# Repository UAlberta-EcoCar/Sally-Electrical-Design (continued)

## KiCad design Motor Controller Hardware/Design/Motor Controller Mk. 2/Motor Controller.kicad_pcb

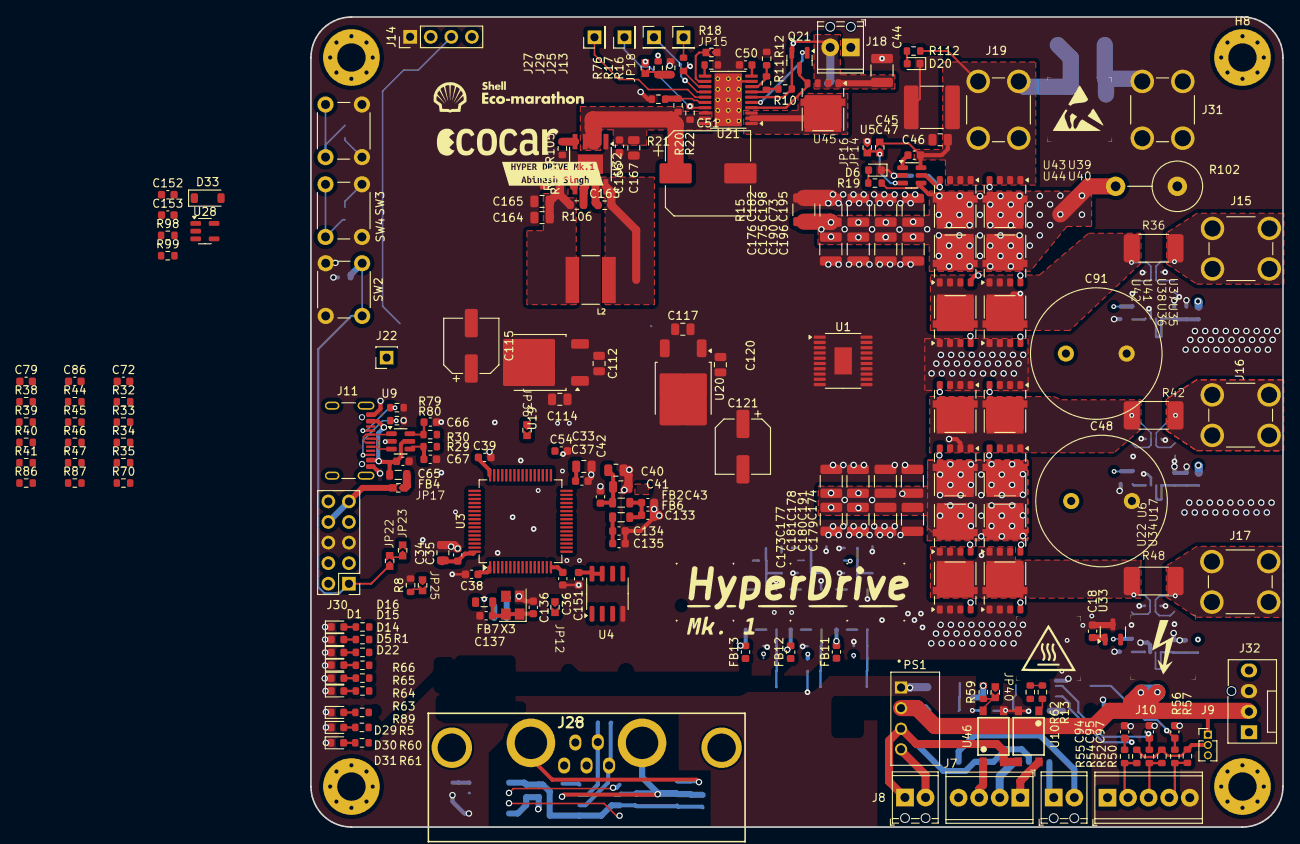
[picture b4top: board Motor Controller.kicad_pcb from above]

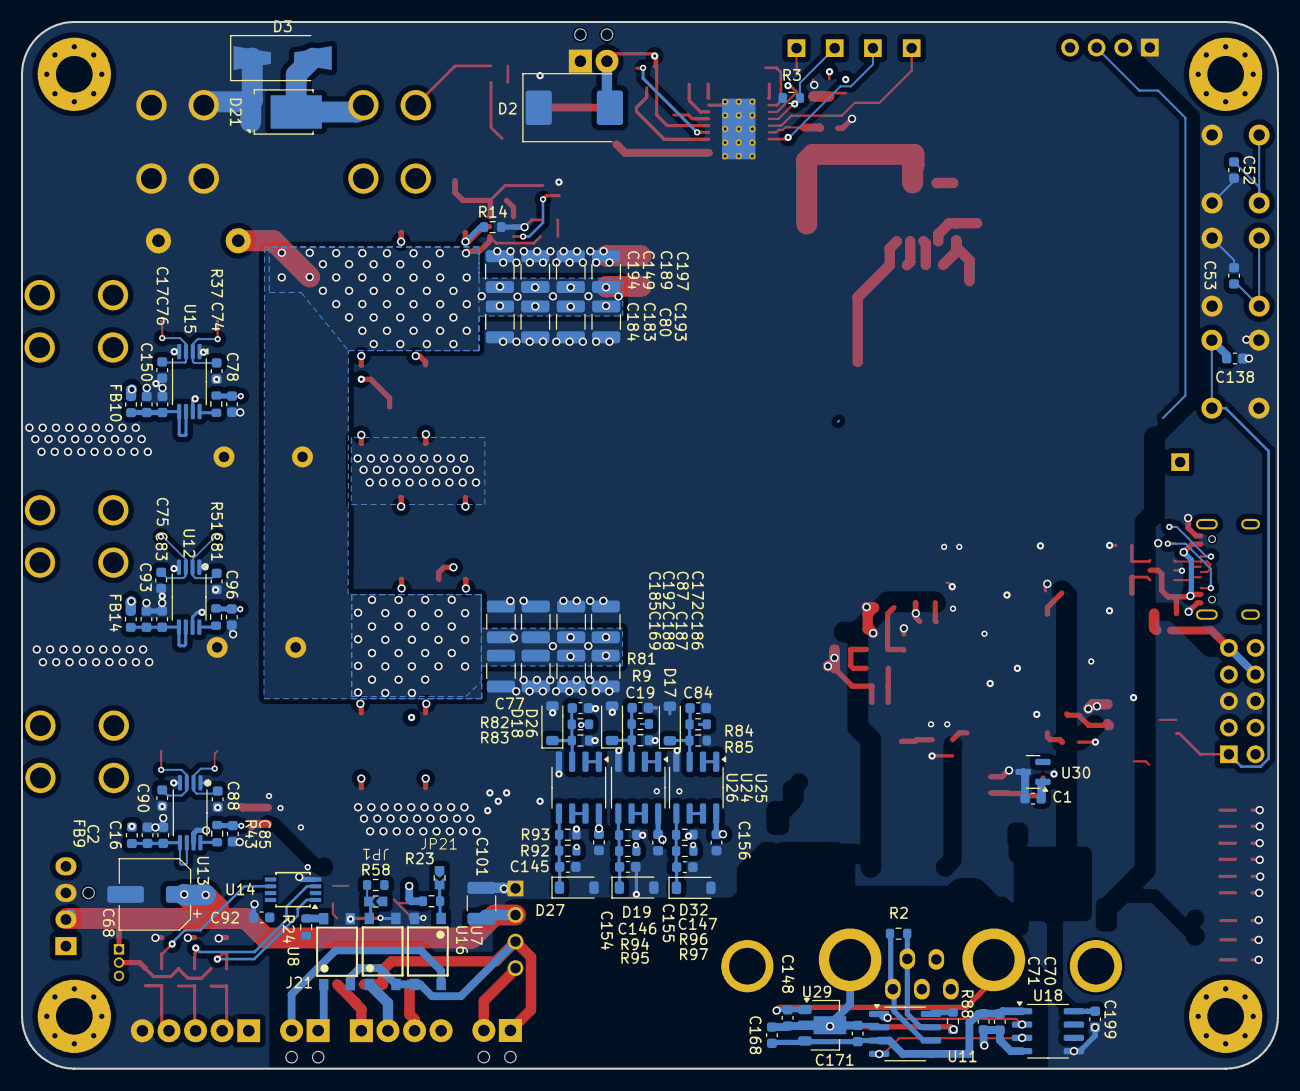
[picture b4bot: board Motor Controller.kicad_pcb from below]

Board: 4 copper layers, 120.0 x 100.0 mm, 320 parts (103 on the bottom side), 167 nets.

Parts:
C1, C2, C16, C17, C18, C35, C36, C37, C38, C39, C42, C43, C47, C50, C52, C53, C54, C65, C70, C71, C75, C92, C93, C133, C135, C136, C137, C138, C150, C151, C153, C154, C155, C156, C166, C171, C199: 100n; C_0603_1608Metric
C19, C77, C84, C145, C146, C147, C152: C; C_0603_1608Metric
C33, C41: 1u; C_0805_2012Metric
C34, C40: 4u7; C_0805_2012Metric
C44, C101, C149, C169, C172, C173, C174, C175, C176, C177, C178, C179, C180, C181, C182, C183, C184, C185, C186, C187, C188, C189, C190, C191, C192, C193, C194, C195, C196, C197, C198: 10u; C_1210_3225Metric
C45: 10u; C_2220_5750Metric
C46: 22n; C_0805_2012Metric
C48, C91: 470u; C_Radial_D16.0mm_H25.0mm_P7.50mm
C51: 100u; CP_Elec_10x10
C66, C67: 47p; C_0603_1608Metric
C68, C115, C121: 100u; CP_Elec_6.3x9.9
C72, C79, C86: 470n; C_0603_1608Metric
C73, C80, C87: 2u2; C_1210_3225Metric
C74, C76, C81, C83, C88, C90: 1n; C_0603_1608Metric
C78, C85, C96: 2n2; C_0603_1608Metric
C94, C95, C97: 100p; C_0603_1608Metric
C112, C114, C117, C120, C165, C167: 10u; C_0805_2012Metric
C134, C148: 1u; C_0603_1608Metric
C163: 100n; R_0603_1608Metric
C164: 47u; C_0805_2012Metric
C168: 2u2; C_0603_1608Metric
D1: GREEN; LED_0603_1608Metric
D2: SMCJ36CA; D_SMC
D3: SMBJ58A; D_SMA-SMB_Universal_Handsoldering
D5, D6, D14, D15, D16, D20, D22, D29, D30, D31: BLUE; LED_0603_1608Metric
D17, D18, D19, D26, D27, D32, D33: MMSZ5226B-7-F; D_SOD-123
D21: D_Schottky; TO-277B
FB2, FB4, FB6, FB7: 600@100MHz 1A; L_0805_2012Metric
FB9, FB10, FB11, FB12, FB13, FB14: 600R@100MHz 1A; L_0603_1608Metric
H7, H8, H9, H10: MountingHole; MountingHole_3.5mm_Pad_Via
J7: Isolated Interface; TerminalBlock_Phoenix_MPT-0,5-4-2.54_1x04_P2.54mm_Horizontal
J8: Interact Power; TerminalBlock_Phoenix_MPT-0,5-2-2.54_1x02_P2.54mm_Horizontal
J9: HALL VCC SEL; PinHeader_1x03_P1.27mm_Vertical
J10: Screw_Terminal_01x03; TerminalBlock_Phoenix_MPT-0,5-5-2.54_1x05_P2.54mm_Horizontal
J11: USB_C_Receptacle_USB2.0_14P; USB_C_Receptacle_GCT_USB4105-xx-A_16P_TopMnt_Horizontal
J13, J25, J27, J29: Conn_01x01_Socket; PinHeader_1x01_P2.54mm_Vertical
J14: Aux Display OLED; PinHeader_1x04_P2.54mm_Vertical
J15: Coil_{U}; KEYSTONE_7691
J16: COIL_{V}; KEYSTONE_7691
J17: COIL_{W}; KEYSTONE_7691
J18: Logic Supply Input; TerminalBlock_Phoenix_MPT-0,5-2-2.54_1x02_P2.54mm_Horizontal
J19: SUPPLY; KEYSTONE_7691
J21: Screw_Terminal_01x02; TerminalBlock_Phoenix_MPT-0,5-2-2.54_1x02_P2.54mm_Horizontal
J22: BUZZER_OUT; PinSocket_1x01_P2.54mm_Vertical
J28: DB7W2-Male
J30: STM32-Prog-Header; PinHeader_2x05_P2.54mm_Vertical
J31: GND; KEYSTONE_7691
J32: Fan; FanPinHeader_1x04_P2.54mm_Vertical
JP1: Controller A EXT Reset EN; J_0603_Triangular
JP12: POWER_STAGE_ENABLE; J_0603_Triangular
JP14: Always ON; J_0603_Triangular
JP15: Active Retry; J_0603_Triangular
JP16: Always OFF; J_0603_Triangular
JP17: Jump 5V; J_0603_Triangular
JP18: ~{SHDN} Enable; J_0603_Triangular
JP21: STATUS_OUT; J_0603_Triangular
JP22: TIE NRST TO EXTNRST; J_0603_Triangular
JP23: SOFTWARE_RESET_CONTROLLER_A; J_0603_Triangular
JP25: BOOT; J_0603_Triangular
JP36, JP40: EXT_DRV_ENABLE; J_0603_Triangular
L2: 22u; IND_ASPI-6045S-2R7N-T
PS1: RFM-0505S; CONV_RFM-0505S
Q21: BSS138; SOT-23
R1: 100R; R_0603_1608Metric
R2: 120R; R_0603_1608Metric
R3: 71k5; R_0603_1608Metric
R5, R19, R37, R43, R50, R51, R54, R56, R60, R61, R63, R64, R65, R66, R89: 1k; R_0603_1608Metric
R8, R14, R34, R35, R40, R41, R46, R47, R76, R81, R83, R85, R88, R99, R104: 10k; R_0603_1608Metric
R9, R82, R84, R98: 147k; R_0603_1608Metric
R10, R11, R12, R16, R17, R18, R20, R21: R; R_0603_1608Metric
R13, R44, R45, R70, R86, R87: 0R; R_0603_1608Metric
R15: 14k; R_1210_3225Metric
R22: 24k; R_0603_1608Metric
R23, R24, R58, R59, R62: 10K; R_0603_1608Metric
R29, R30: 27R; R_0603_1608Metric
R32, R33, R38, R39: 2R2; R_0603_1608Metric
R36, R42, R48: 3m; CSS2H-2512
R52, R55, R57: 4k7; R_0603_1608Metric
R79, R80: 5k1; R_0603_1608Metric
R90: 60k4; R_0603_1608Metric
R92, R94, R96: 5k; R_0603_1608Metric
R93, R95, R97: 9k76; R_0603_1608Metric
R102: 14k; R_Axial_DIN0617_L17.0mm_D6.0mm_P7.62mm_Vertical
R105: 64k9; R_0603_1608Metric
R106: 100k; R_0603_1608Metric
R112: 13k; R_0603_1608Metric
SW2: NRST; SW_PUSH_6mm
SW3: GPBTN_1; SW_PUSH_6mm
SW4: GPBTN_2; SW_PUSH_6mm
U1: DRV8300NPWR; TSSOP-20-1EP_4.4x6.5mm_P0.65mm_EP2.15x3.35mm
U3: STM32G474RET6; LQFP-64_10x10mm_P0.5mm
U4: M95256-WMN6P; SOIC-8_3.9x4.9mm_P1.27mm
U5: LM74700QDBVTQ1; SOT-23-6
U6, U17, U22, U34, U35, U36, U37, U38, U39, U40, U41, U42, U43, U44, U45: NTMFS4D0N08XT1G; PowerMosDFNHybrid
U7, U8, U10, U16, U46: WL-OCPT-140357145200; WL-OCPT_SOP4
U9: USBLC6-2SC6; SOT-23-6
U11: MCP2542FD-E/SN; SOIC-8_3.9x4.9mm_P1.27mm
U12, U13, U15: INA240A3PW; TSSOP-8_4.4x3mm_P0.65mm
U14: 74LVC3G17; TSSOP-8_3x3mm_P0.65mm
U18: ISO6521D; SOIC-8_3.9x4.9mm_P1.27mm
U19: AZ1084-5.0; TO-252-2
U20: AZ1084-3.3; TO-252-2
U21: TPS26631PWP; HTSSOP-20-1EP_4.4x6.5mm_P0.65mm_EP3.4x6.5mm_Mask2.96x2.96mm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
U24, U25, U26: TSV912IDT; SOIC-8_3.9x4.9mm_P1.27mm
U28: TSV911RILT; SOT-23-5
U29: AP2205-5.0; SOT-89-3
U30, U33: MCP9700AT-ETT; SOT-23
U32: LMR38020; TI_SO-PowerPAD-8
X3: 8MHz; Crystal_SMD_3225-4Pin_3.2x2.5mm
kibuzzard-6768F62A: G***; kibuzzard-6768F62A

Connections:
5V_ISOLATED: J8.2, PS1.4 (+VOUT)
+3.3VA: C40.1, C41.1, C42.1, FB2.2, U3.29 (VDDA)
+3V3: C1.2, C18.2, C33.1, C34.1, C35.1, C36.1, C37.1, C38.1, C39.1, C43.1, C92.1, C120.1, C121.1, C133.1, C151.1, C199.1, FB2.1, FB6.1, FB7.2, FB11.1, FB12.1, FB13.1, J9.3, J30.7 (3.3V), J30.10 (5V), R23.2, R24.2, R58.2, R59.2, R61.1, R62.2, U3.1 (VBAT), U3.16 (VDD), U3.32 (VDD), U3.48 (VDD), U3.64 (VDD), U4.7 (~HOLD), U4.8 (VCC), U14.8 (VCC), U18.8 (VCC2), U20.2 (VO), U30.1 (V_{DD}), U33.1 (V_{DD})
+5V: C68.1, C101.1, C114.1, C115.1, C117.1, C153.1, FB9.1, FB10.1, FB14.1, J9.1, J14.2, J30.8 (3.3V), J30.9 (5V), J32.2, JP17.2 (B), PS1.2 (+VIN), R60.1, U19.2 (VO), U20.3 (VI), U28.2 (V+)
+12V: C112.1, C164.1, C165.1, L2.2, R5.1, R90.1, R106.2, U19.3 (VI)
/Comunications/5V: C70.1, C71.1, C168.1, C171.1, U11.3 (VDD), U11.5 (VIO), U18.1 (VCC1), U29.3 (VOUT)
/Comunications/CAN Bus Interface/CAN_H+: J28.2, R2.1, U11.7 (CANH)
/Comunications/CAN Bus Interface/CAN_L-: J28.5, R2.2, U11.6 (CANL)
/Comunications/CAN Bus Interface/CAN_STBY: R88.1, U11.8 (STBY)
/Comunications/CAN Bus Interface/SYS_7V: C148.1, J28.8 (A1), U29.1 (VIN)
/Comunications/CAN Bus Interface/SYS_12V: J28.1, J28.3, J28.4
/Comunications/CAN_RXD_ISO: U3.56 (PB3), U18.6 (OUTB)
/Comunications/CAN_RXD_SYS: U11.4 (RXD), U18.3 (INB)
/Comunications/CAN_TXD_ISO: U3.57 (PB4), U18.7 (INA)
/Comunications/CAN_TXD_SYS: U11.1 (TXD), U18.2 (OUTA)
/Comunications/USB_D+: R29.2, U3.46 (PA12)
/Comunications/USB_D-: R30.2, U3.45 (PA11)
/Controller_B_ANALOG_SPEED: C54.1, R24.1, U3.34 (PB12), U8.4
/Controller_B_STATUS: JP21.1 (A), R1.2, U3.30 (PB10)
/EXT_DRV_EN_IN: JP36.1 (A), JP40.1 (A)
/EXT_NRST_Controllers: JP1.1 (A), JP22.2 (B), JP23.1 (A)
/EXT_POWER_STAGE_EN_IN: JP12.2 (B), JP14.1 (A), JP16.2 (B), U5.3 (EN)
/GATE_DRIVER_FAULT_OUT: R13.1, R62.1, U3.51 (PA15)
/HALL_U: U3.12 (PA0), U14.2 (3Y)
/HALL_V: U3.13 (PA1), U14.5 (2Y)
/HALL_W: U3.14 (PA2), U14.7 (1Y)
/I_{U,_BUFFERED}: U3.20 (PA6), U25.6 (-), U25.7
/I_{V,_BUFFERED}: U3.21 (PA7), U24.6 (-), U24.7
/I_{W,_BUFFERED}: U3.22 (PC4), U26.6 (-), U26.7
/Isolated Driver Interface/Controller_STATUS_ISO: J21.2, U7.4
/Isolated Driver Interface/EXT_ANALOG_SPEED_ISO: J21.1, U8.1
/Isolated Driver Interface/EXT_DRV_EN_IN_ISO: J7.3, U46.1
/Isolated Driver Interface/EXT_NRST_Controllers_IN_ISO: J7.2, U16.1
/Isolated Driver Interface/FAULT_OUT_ISO: J7.1, U10.4
/Low Power Current Monitor: J25.1, R3.1, U3.33 (PB11), U21.14 (IMON)
/Microcontroller/BOOT0: JP25.1 (A), U3.61 (PB8)
/Microcontroller/BUZZER: J22.1, U3.25 (PB1)
/Microcontroller/CLK: U3.5 (PF0), X3.3 (OUT)
/Microcontroller/CNTRL_TMP_SNS: U3.24 (PB0), U30.2 (V_{OUT})
/Microcontroller/GPBTN_1: C52.1, SW3.1, U3.8 (PC0)
/Microcontroller/GPBTN_2: C53.1, JP23.2 (B), SW4.1, U3.55 (PD2)
/Microcontroller/GPLED_1: R89.1, U3.4 (PC15)
/Microcontroller/GPLED_2: R63.1, U3.3 (PC14)
/Microcontroller/GPLED_3: R64.1, U3.2 (PC13)
/Microcontroller/GPLED_4: R65.1, U3.62 (PB9)
/Microcontroller/GPLED_5: R66.1, U3.6 (PF1)
/Microcontroller/I2C3_SCL: J14.3, U3.40 (PC8)
/Microcontroller/I2C3_SDA: J14.4, U3.41 (PC9)
/Microcontroller/NRST: C138.1, J30.1 (RST), JP22.1 (A), SW2.1, U3.7 (PG10)
/Microcontroller/PWR_TMP_SNS: U3.23 (PC5), U33.2 (V_{OUT})
/Microcontroller/SWCLK: J30.2 (SWCLK), U3.50 (PA14)
/Microcontroller/SWDIO: J30.4 (SWDIO), U3.49 (PA13)
/Microcontroller/~MEM_CS: U3.58 (PB5), U4.1 (~S)
/Motor Gate Driver/BSTA: C72.2, U1.20 (BSTA)
/Motor Gate Driver/BSTB: C79.2, U1.17 (BSTB)
/Motor Gate Driver/BSTC: C86.2, U1.14 (BSTC)
/Motor Gate Driver/Coil Drive U/+3V3_Filtered: C154.1, FB11.2, U25.8 (V+)
/Motor Gate Driver/Coil Drive U/COIL_{U}: C76.1, J15.1, R36.2, R82.1, U15.3 (-)
/Motor Gate Driver/Coil Drive U/I_{U}: C78.1, R37.2, R92.1
/Motor Gate Driver/Coil Drive U/V_{SENSE, U, 1}: C74.1, R36.1, R70.2, U15.2 (+), U39.1 (S), U39.2 (S), U39.3 (S), U40.1 (S), U40.2 (S), U40.3 (S), U41.5 (D), U42.5 (D)
/Motor Gate Driver/Coil Drive V/+3V3_Filtered: C155.1, FB12.2, U24.8 (V+)
/Motor Gate Driver/Coil Drive V/COIL_{V}: C83.1, J16.1, R9.1, R42.2, U12.3 (-)
/Motor Gate Driver/Coil Drive V/I_{V}: C96.1, R51.2, R94.1
/Motor Gate Driver/Coil Drive V/V_{SENSE, V, 1}: C81.1, R42.1, R86.2, U12.2 (+), U35.1 (S), U35.2 (S), U35.3 (S), U36.1 (S), U36.2 (S), U36.3 (S), U37.5 (D), U38.5 (D)
/Motor Gate Driver/Coil Drive W/+3V3_Filtered: C156.1, FB13.2, U26.8 (V+)
/Motor Gate Driver/Coil Drive W/COIL_{W}: C90.1, J17.1, R48.2, R84.1, U13.3 (-)
/Motor Gate Driver/Coil Drive W/I_{W}: C85.1, R43.2, R96.1
/Motor Gate Driver/Coil Drive W/VD+: C88.1, R48.1, R87.2, U6.1 (S), U6.2 (S), U6.3 (S), U13.2 (+), U17.1 (S), U17.2 (S), U17.3 (S), U22.5 (D), U34.5 (D)
/Motor Gate Driver/GHA: R32.1, R34.2, U1.19 (GHA)
/Motor Gate Driver/GHB: R38.1, R40.2, U1.16 (GHB)
/Motor Gate Driver/GHC: R44.1, R46.2, U1.13 (GHC)
/Motor Gate Driver/GLA: R33.1, R35.2, U1.11 (GLA)
/Motor Gate Driver/GLB: R39.1, R41.2, U1.10 (GLB)
/Motor Gate Driver/GLC: R45.1, R47.2, U1.9 (GLC)
/Motor Gate Driver/SHA: C72.1, R70.1, U1.18 (SHA)
/Motor Gate Driver/SHB: C79.1, R86.1, U1.15 (SHB)
/Motor Gate Driver/SHC: C86.1, R87.1, U1.12 (SHC)
/Position Sensing/HALL_U_RAW: J10.4, R56.2, R57.1
/Position Sensing/HALL_V_RAW: J10.3, R54.2, R55.1
/Position Sensing/HALL_W_RAW: J10.2, R50.2, R52.1
/Power Delivery/IN_SYS: C44.1, D2.2 (A2), J18.2, Q21.2 (S), R10.1, R16.1, U21.6 (IN_SYS), U45.1 (S), U45.2 (S), U45.3 (S)
/Power Delivery/Motor Supply Unprotected: C45.1, C46.1, C47.2, D3.2 (A2), D21.3 (K), J19.1, JP14.2 (B), R112.1, U5.6 (ANODE), U43.1 (S), U43.2 (S), U43.3 (S), U44.1 (S), U44.2 (S), U44.3 (S)
/Power Delivery/Motor_Controller_Power_Good: J29.1, R22.2, U21.17 (PGOOD)
/Power Delivery/~Low Side Fault: J27.1, U21.15 (~FLT)
/Power Delivery/~SHDN: JP18.1 (A), R76.1, U21.13 (~SHDN)
/SPI_MISO: U3.53 (PC11), U4.2 (Q)
/SPI_MOSI: U3.54 (PC12), U4.5 (D)
/SPI_SCK: U3.52 (PC10), U4.6 (C)
/V_{M}_BUFFERED: U28.1, U28.4 (-)
/V_{SENSE,_U,_BUFFERED}: U3.17 (PA3), U25.1, U25.2 (-)
/V_{SENSE,_V,_BUFFERED}: U3.18 (PA4), U24.1, U24.2 (-)
/V_{SENSE,_W,_BUFFERED}: U3.19 (PA5), U26.1, U26.2 (-)
GND: C1.1, C2.2, C16.2, C17.2, C18.1, C19.2, C33.2, C34.2, C35.2, C36.2, C37.2, C38.2, C39.2, C40.2, C41.2, C42.2, C43.2, C44.2, C45.2, C46.2, C50.2, C51.2, C52.2, C53.2, C54.2, C65.1, C66.2, C67.2, C68.2, C73.2, C74.2, C75.2, C76.2, C77.2, C78.2, C80.2, C81.2, C83.2, C84.2, C85.2, C87.2, C88.2, C90.2, C92.2, C93.2, C94.2, C95.2, C96.2, C97.2, C101.2, C112.2, C114.2, C115.2, C117.2, C120.2, C121.2, C133.2, C134.2, C135.2, C136.2, C137.2, C138.2, C145.2, C146.2, C147.2, C150.2, C151.2, C152.2, C153.2, C154.2, C155.2, C156.2, C164.2, C165.2, C166.2, C167.2, C199.2, D1.1 (K), D2.1 (A1), D3.1 (A1), D5.1 (K), D6.1 (K), D14.1 (K), D15.1 (K), D16.1 (K), D17.2 (A), D18.2 (A), D19.2 (A), D20.1 (K), D21.1 (A), D21.2 (A), D22.1 (K), D26.2 (A), D27.2 (A), D29.1 (K), D30.1 (K), D31.1 (K), D32.2 (A), D33.2 (A), J10.5, J11.A1 (GND), J11.A12 (GND), J11.B1 (GND), J11.B12 (GND), J14.1, J18.1, J30.5 (GND), J30.6 (GND), J31.1, J32.3, JP15.1 (A), JP16.1 (A), PS1.1 (-VIN), R3.2, R8.2, R12.2, R14.2, R17.2, R18.2, R21.2, R34.1, R35.1, R40.1, R41.1, R46.1, R47.1, R79.2, R80.2, R81.1, R83.1, R85.1, R93.1, R95.1, R97.1, R99.1, R104.2, R105.2, SW2.2, SW3.2, SW4.2, U1.8 (GND), U3.15 (VSS), U3.27 (VSSA), U3.31 (VSS), U3.47 (VSS), U3.63 (VSS), U4.4 (VSS), U5.2 (GND), U7.2, U8.3, U9.2 (GND), U10.2, U12.1 (GND), U12.4 (GND), U12.7 (REF1), U13.1 (GND), U13.4 (GND), U13.7 (REF1), U14.4 (GND), U15.1 (GND), U15.4 (GND), U15.7 (REF1), U16.3, U18.5 (GND2), U19.1 (GND), U20.1 (GND), U21.9 (GND), U21.21 (GND), U22.1 (S), U22.2 (S), U22.3 (S), U24.4 (V-), U25.4 (V-), U26.4 (V-), U28.5 (V-), U30.3 (GND), U32.1 (GND), U32.9 (EP), U33.3 (GND), U34.1 (S), U34.2 (S), U34.3 (S), U37.1 (S), U37.2 (S), U37.3 (S), U38.1 (S), U38.2 (S), U38.3 (S), U41.1 (S), U41.2 (S), U41.3 (S), U42.1 (S), U42.2 (S), U42.3 (S), U46.3, X3.2 (GND)
GND1: J8.1, PS1.3 (-VOUT), U7.3, U8.2, U10.3, U16.2, U46.2
GND2: C70.2, C71.2, C148.2, C168.2, C171.2, J28.9 (A2), R88.2, U11.2 (VSS), U18.4 (GND1), U29.2 (GND)
GNDPWR: C48.2, C91.2, C149.2, C169.2, C172.2, C173.2, C174.2, C175.2, C176.2, C177.2, C178.2, C179.2, C180.2, C181.2, C182.2, C183.2, C184.2, C185.2, C186.2, C187.2, C188.2, C189.2, C190.2, C191.2, C192.2, C193.2, C194.2, C195.2, C196.2, C197.2, C198.2, R15.2, R102.1
Logic Power Protected: C51.1, C166.1, C167.1, R20.1, R22.1, U21.18 (OUT), U21.19 (OUT), U21.20 (OUT), U32.2 (EN), U32.3 (VIN)
unnamed: C66.1, R30.1, U9.6 (I/O1)
unnamed: C67.1, R29.1, U9.4 (I/O2)
unnamed: D1.2 (A), R1.1
unnamed: D5.2 (A), R63.2
unnamed: D6.2 (A), R19.2
unnamed: R44.2, U6.4 (G), U17.4 (G)
unnamed: R38.2, U35.4 (G), U36.4 (G)
unnamed: R39.2, U37.4 (G), U38.4 (G)
unnamed: R32.2, U39.4 (G), U40.4 (G)
unnamed: R33.2, U41.4 (G), U42.4 (G)
unnamed: R45.2, U22.4 (G), U34.4 (G)
unnamed: D14.2 (A), R64.2
unnamed: D15.2 (A), R65.2
unnamed: D16.2 (A), R66.2
unnamed: C84.1, D17.1 (K), R84.2, R85.2, U26.3 (+)
unnamed: C19.1, D18.1 (K), R9.2, R81.2, U24.3 (+)
unnamed: C146.1, D19.1 (K), R94.2, R95.2, U24.5 (+)
unnamed: D20.2 (A), R112.2
unnamed: D22.2 (A), R89.2
unnamed: C77.1, D26.1 (K), R82.2, R83.2, U25.3 (+)
unnamed: C145.1, D27.1 (K), R92.2, R93.2, U25.5 (+)
unnamed: D29.2 (A), R5.2
unnamed: D30.2 (A), R60.2
unnamed: D31.2 (A), R61.2
unnamed: C147.1, D32.1 (K), R96.2, R97.2, U26.5 (+)
unnamed: C152.1, D33.1 (K), R98.2, R99.2, U28.3 (+)
unnamed: J9.2, J10.1, R52.2, R55.2, R57.2
unnamed: J11.A5 (CC1), R79.1
unnamed: J11.B5 (CC2), R80.1
unnamed: J11.A6 (D+), J11.B6 (D+), U9.3 (I/O2)
unnamed: J11.A7 (D-), J11.B7 (D-), U9.1 (I/O1)
unnamed: J13.1, R76.2
unnamed: JP1.2 (B), R58.1, U16.4
unnamed: JP12.1 (A), U3.26 (PB2)
unnamed: JP15.2 (B), U21.12 (MODE)
unnamed: JP18.2 (B), R16.2, R17.1
unnamed: JP21.2 (B), R23.1, U7.1
unnamed: JP25.2 (B), R8.1
unnamed: JP36.2 (B), U3.39 (PC7)
unnamed: JP40.2 (B), R59.1, U46.4
unnamed: Q21.3 (D), U21.4 (B_GATE), U45.4 (G)
unnamed: Q21.1 (G), U21.5 (DRV)
unnamed: R13.2, U10.1
unnamed: R37.1, U15.8
unnamed: R43.1, U13.8
unnamed: R51.1, U12.8
unnamed: C47.1, U5.1 (VCAP)
unnamed: C65.2, FB4.1, J11.A4 (VBUS), J11.A9 (VBUS), J11.B4 (VBUS), J11.B9 (VBUS), U9.5 (VBUS)
unnamed: C75.1, C93.1, FB14.2, U12.5 (V+), U12.6 (REF2)
unnamed: C2.1, C16.1, FB9.2, U13.5 (V+), U13.6 (REF2)
unnamed: C94.1, R50.1, U14.1 (1A)
unnamed: C95.1, R54.1, U14.3 (2A)
unnamed: C97.1, R56.1, U14.6 (3A)
unnamed: C17.1, C150.1, FB10.2, U15.5 (V+), U15.6 (REF2)
unnamed: R18.1, U21.11 (ILIM)
unnamed: R11.2, R12.1, U21.8 (OVP)
unnamed: R20.2, R21.1, U21.16 (PGTH)
unnamed: R10.2, R11.1, U21.7 (UVLO)
unnamed: C50.1, U21.10 (dVdT)
unnamed: C163.1, U32.7 (BOOT)
unnamed: R90.2, R104.1, U32.5 (FB)
unnamed: R106.1, U32.6 (PG)
unnamed: R105.1, U32.4 (RT/SYNC)
unnamed: C163.2, L2.1, U32.8 (SW)
unnamed: R14.1, U5.5 (GATE), U43.4 (G), U44.4 (G)
unnamed: U21.1 (IN), U21.2 (IN), U21.3 (IN), U45.5 (D)
unnamed: C136.1, C137.1, FB7.1, X3.1 (EN), X3.4 (Vdd)
VBUS: FB4.2, JP17.1 (A)
VREFP: C134.1, C135.1, FB6.2, U3.28 (VREF+)
V_{M}: C48.1, C73.1, C80.1, C87.1, C91.1, C149.1, C169.1, C172.1, C173.1, C174.1, C175.1, C176.1, C177.1, C178.1, C179.1, C180.1, C181.1, C182.1, C183.1, C184.1, C185.1, C186.1, C187.1, C188.1, C189.1, C190.1, C191.1, C192.1, C193.1, C194.1, C195.1, C196.1, C197.1, C198.1, R15.1, R19.1, R98.1, R102.2, U5.4 (CATHODE), U6.5 (D), U17.5 (D), U35.5 (D), U36.5 (D), U39.5 (D), U40.5 (D), U43.5 (D), U44.5 (D)

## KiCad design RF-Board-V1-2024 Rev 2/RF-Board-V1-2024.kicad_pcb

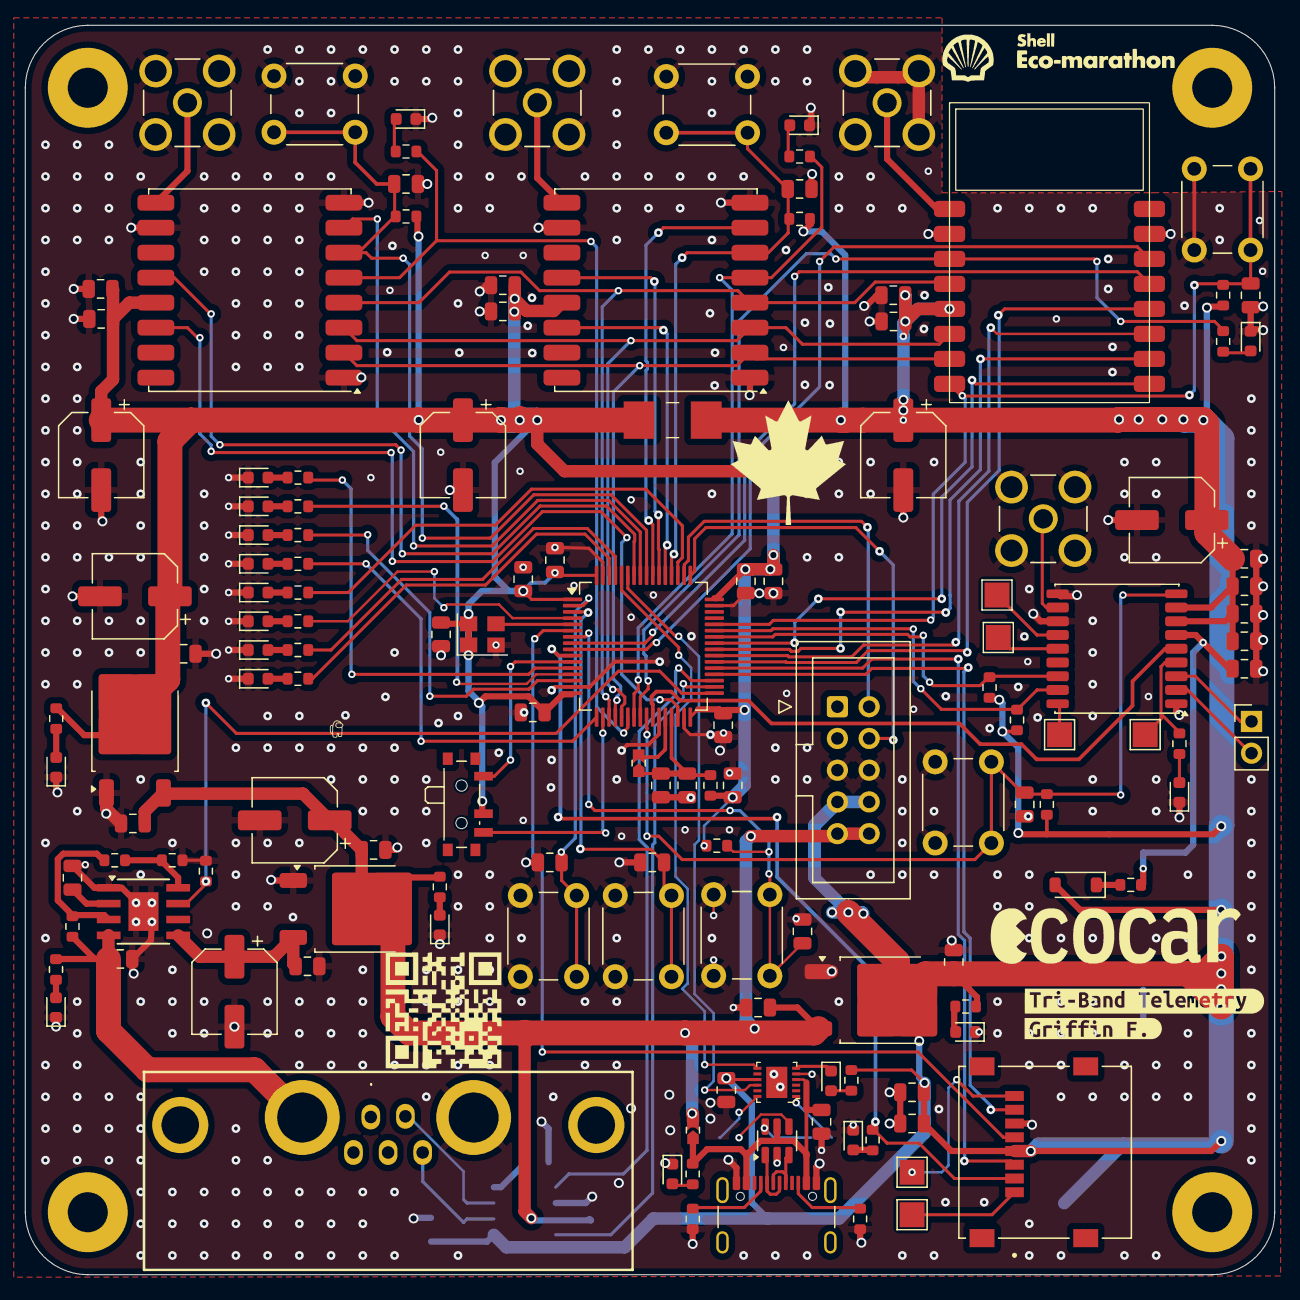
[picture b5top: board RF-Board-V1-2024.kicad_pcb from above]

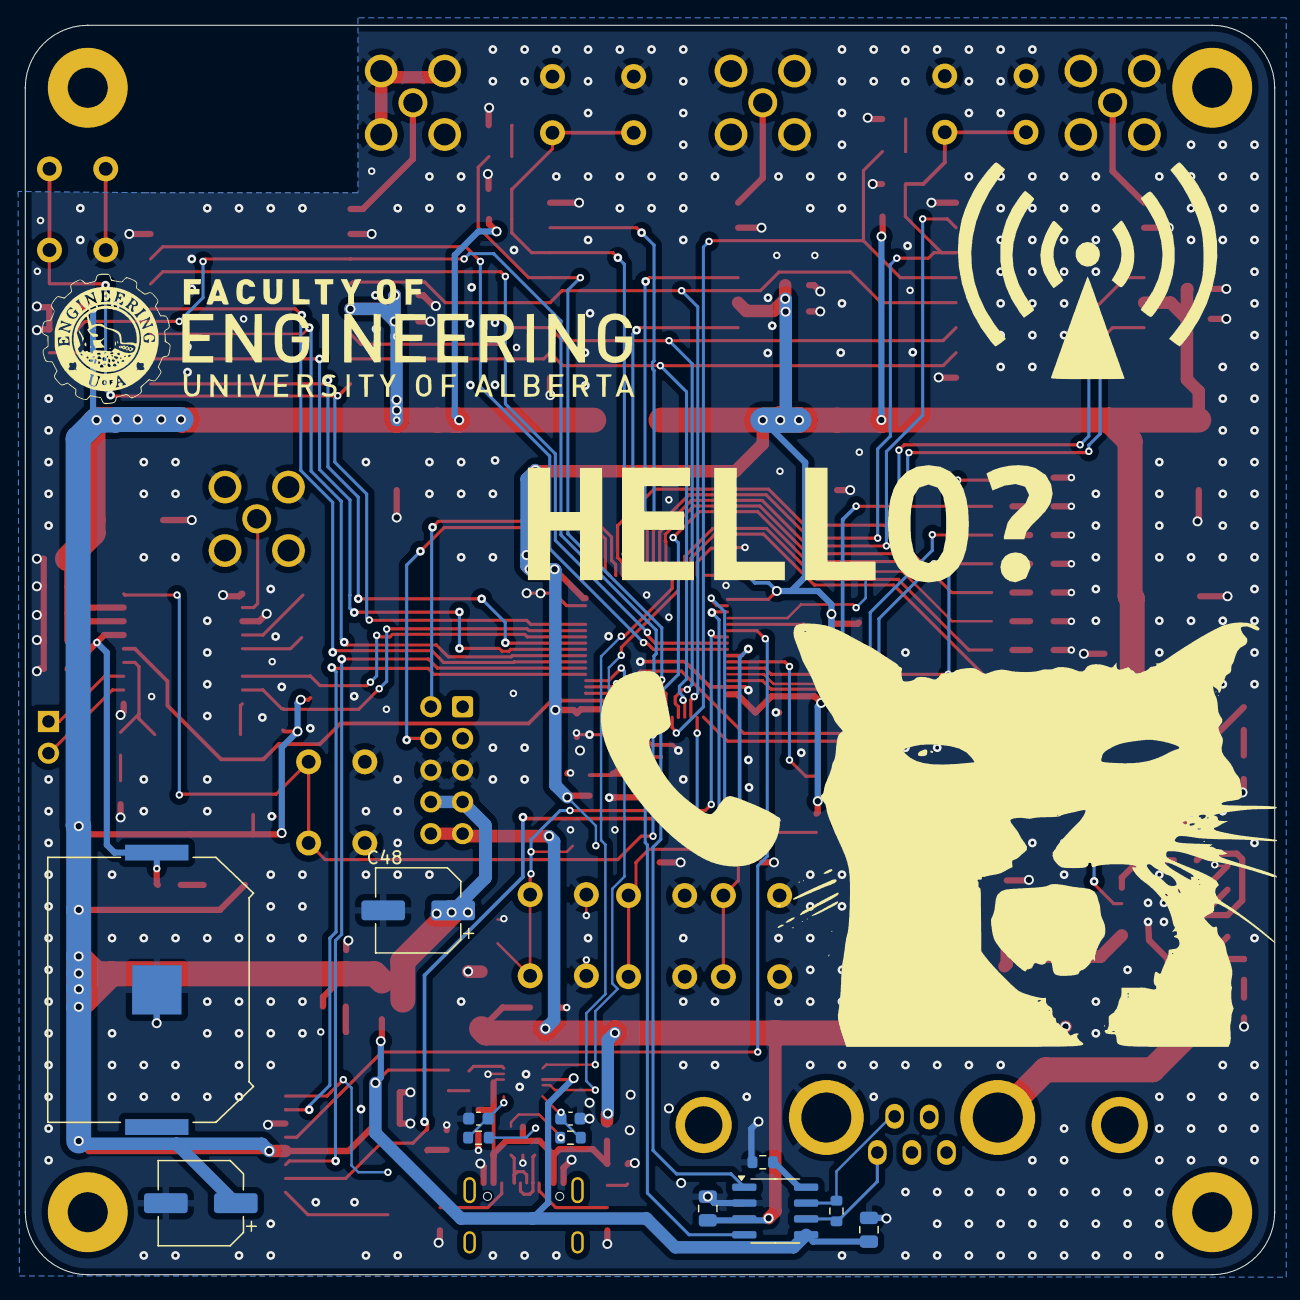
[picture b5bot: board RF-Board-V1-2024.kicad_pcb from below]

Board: 2 copper layers, 100.0 x 100.0 mm, 158 parts (13 on the bottom side), 106 nets.

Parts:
BT1: 3034TR; BAT_3034TR
C1, C9, C12, C15, C16, C18, C22, C39, C46: 10u; C_0805_2012Metric
C2, C10, C47: 22u; C_0805_2012Metric
C3, C4, C8, C14, C17, C31, C32, C40, C48: 100u; CP_Elec_6.3x5.9
C5, C29, C30, C42: 1u; C_0805_2012Metric
C6, C11, C13, C19, C20, C21, C23, C24, C25, C26, C27, C28, C33, C34, C35, C36, C37, C38, C41, C43, C44, C45, C49, C50, C53: 100n; C_0805_2012Metric
C7: 2n2; C_0805_2012Metric
C51, C52: 47p; C_0603_1608Metric
D1, D3, D4, D5, D6, D8, D9, D10, D11, D12, D13, D14, D15, D16, D17, D18, D19, D20: LED; LED_0603_1608Metric
D2: BLUE; LED_0603_1608Metric
D7: 0.5A/40V/420mV; D_SOD-123
FB2: 120R; R_0603_1608Metric
H1, H2, H3, H4: MountingHole_3.2mm_M3_Pad
J1: DB7W2-Male
J2, J3, J6: RFPC-SMA29-F; GRADCONN_RFPC-SMA29-F
J4: UART; PinHeader_1x02_P2.54mm_Vertical
J5: RFPC-SMA28-F; GRADCONN_RFPC-SMA28-F
J7: STM32-Prog-Header; IDC-STM32-Prog-Header_2x05_P2.54mm_Vertical
J8: USB_C_Receptacle_USB2.0_14P; USB_C_Receptacle_GCT_USB4105-xx-A_16P_TopMnt_Horizontal
J9: MSD-10-C; CUI_MSD-10-C
JP1, JP2: Jumper_2_Open; J_0603_Triangular
JP4: Jumper_2_Open; Jumper_Micro-Miniature_P5.375mm
R1, R2: 5k1; R_0603_1608Metric
R3, R21: 2k; R_0603_1608Metric
R4: 150; R_0603_1608Metric
R5: 120; R_0603_1608Metric
R6: 287K; R_0603_1608Metric
R7: 57K; R_0603_1608Metric
R8: 47k; R_0603_1608Metric
R9: 1k1; R_0603_1608Metric
R10, R12, R14, R15, R17, R18, R31, R34: 600; R_0603_1608Metric
R11, R13: 2k2; R_0603_1608Metric
R16: 3k3; R_0603_1608Metric
R19, R26: 10k; R_0603_1608Metric
R20, R22, R23, R24, R25, R30, R32, R33, R37: 1k; R_0603_1608Metric
R27, R28, R29: 0R; R_0603_1608Metric
R35, R36: 27R; R_0603_1608Metric
RF1: MAX-M10S; ublox_MAX
RF2: VG2392S240X0M2; Vollgo VG2392S240X0M2
RF3: DL-RFM69HC-915M; HOPERF_RFM9XW_SMD
RF4: RFM95W-868S2; HOPERF_RFM9XW_SMD
SW1, SW2, SW3, SW4, SW5, SW6, SW8: SW_SPST; SW_PUSH_6mm
SW7: SW_DPDT_x2; SW_SPDT_PCM12
TP1, TP2, TP3, TP4, TP5, TP6: TestPoint; TestPoint_Pad_2.0x2.0mm
U1, U2: AZ1084-3.3; TO-252-2
U3: TPS2596; TI_SO-PowerPAD-8
U4: AZ1084-5.0; TO-252-2
U5: MCP2542FD; SOIC-8_3.9x4.9mm_P1.27mm
U6: STM32G484RET6; LQFP-64_10x10mm_P0.5mm
U7: USBLC6-2SC6; SOT-23-6
U8: FT234XD-R; DFN-12-1EP_3x3mm
X1: OXETDLJANF-8MHZ; Crystal_SMD_3225-4Pin_3.2x2.5mm
kibuzzard-679868A6: G***; kibuzzard-679868A6
kibuzzard-6798610B: G***; kibuzzard-6798610B
kibuzzard-6798611E: G***; kibuzzard-6798611E

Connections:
+3.3V: C2.1, C4.1, C11.2, C12.2, C13.1, C14.1, C15.2, C16.2, C17.1, C18.2, C19.2, C20.2, C21.2, C22.1, C23.1, C24.1, C25.1, C26.1, C27.1, C30.1, C31.1, C32.1, C33.2, C34.2, C35.2, C39.2, C40.1, C41.2, C47.1, C48.1, C49.1, D7.2 (A), FB2.2, J7.7 (3.3V), J7.8 (3.3V), J9.04 (VDD), JP4.1 (A), JP4.2 (B), R10.1, R11.1, R13.1, R26.1, R27.1, R28.1, R29.1, R31.1, R34.1, R37.2, RF1.7 (VCC_IO), RF1.8 (VCC), RF2.5 (VCC), RF3.13 (3.3V), RF4.13 (3.3V), SW7.2 (B), U1.2 (VO), U2.2 (VO), U5.5 (VIO), U6.1 (VBAT), U6.16 (VDD), U6.32 (VDD), U6.48 (VDD), U6.64 (VDD), U8.9 (VCCIO), X1.1 (Tri-State), X1.4 (VDD)
+5V: C1.1, C3.1, C5.1, C10.1, C46.1, J7.9 (5V), J7.10 (5V), JP1.2 (B), R3.1, U1.3 (VI), U2.3 (VI), U4.2 (VO), U5.3 (VDD)
/24.BUSY: RF2.9 (BUSY), U6.41 (PC9)
/24.DIO1: RF2.10 (DIO1), U6.40 (PC8)
/24.DIO2: RF2.11 (DIO2), U6.39 (PC7)
/24.DIO3: RF2.12 (DIO3), U6.38 (PC6)
/24.NSS: R18.1, RF2.3 (NSS), U6.24 (PB0)
/24.RST: C44.1, R27.2, RF2.8 (RST), SW5.2 (B), U6.44 (PA10)
/24.RXEN: RF2.14 (RXEN), U6.9 (PC1)
/24.TXEN: RF2.13 (TXEN), U6.8 (PC0)
/868.DIO0: RF4.14 (DIO0), U6.53 (PC11)
/868.DIO4: RF4.12 (DIO4), U6.54 (PC12)
/868.DIO5: RF4.7 (DIO5), U6.55 (PD2)
/868.MISO: RF2.7 (MISO), RF3.2 (MISO), RF4.2 (MISO), U6.20 (PA6)
/868.MOSI: RF2.6 (MOSI), RF3.3 (MOSI), RF4.3 (MOSI), U6.21 (PA7)
/868.NSS: R12.1, RF4.5 (NSS), U6.23 (PC5)
/868.RST: C45.1, R29.2, RF4.6 (RESET), SW6.2 (B), U6.52 (PC10)
/868.SCK: RF2.4 (SCK), RF3.4 (SCK), RF4.4 (SCK), U6.19 (PA5)
/915.DIO0: RF3.14 (DIO0), U6.30 (PB10)
/915.DIO4: RF3.12 (DIO4), U6.58 (PB5)
/915.DIO5: RF3.7 (DIO5), U6.57 (PB4)
/915.NSS: R15.1, RF3.5 (NSS), U6.22 (PC4)
/915.RST: C38.1, R28.2, RF3.6 (RESET), SW3.2 (B), U6.56 (PB3)
/CAN_RX: U5.4 (RXD), U6.34 (PB12)
/CAN_TX: U5.1 (TXD), U6.35 (PB13)
/GNSS.EXTINT: RF1.5 (EXTINT), U6.26 (PB2)
/GNSS.I2CSCL: R13.2, RF1.17 (SCL), U6.43 (PA9)
/GNSS.I2CSDA: R11.2, RF1.16 (SDA), U6.42 (PA8)
/GPIO_BTN1: C36.1, SW1.2 (B), U6.2 (PC13)
/GPIO_BTN2: C37.1, SW2.2 (B), U6.3 (PC14)
/GPIO_LED1: R20.2, U6.12 (PA0)
/GPIO_LED2: R22.2, U6.13 (PA1)
/GPIO_LED3: R23.2, U6.14 (PA2)
/GPIO_LED4: R24.2, U6.17 (PA3)
/GPIO_LED5: R25.2, U6.51 (PA15)
/GPIO_LED6: R30.2, U6.4 (PC15)
/GPIO_LED7: R32.2, U6.61 (PB8)
/GPIO_LED8: R33.2, U6.62 (PB9)
/GPIO_SWT1: SW7.1 (A), U6.11 (PC3)
/GPIO_SWT2: SW7.3 (C), U6.18 (PA4)
/IMON: R9.1, U3.7 (ILM), U6.33 (PB11)
/NRESET: C53.1, R37.1, SW8.2 (B), U6.7 (PG10)
/Power_CAN/7V_UnProtected: C6.1, J1.8 (A1), R4.1, R6.2, U3.4 (IN)
/Power_CAN/CAN_H: J1.2, R5.1, U5.7 (CANH)
/Power_CAN/CAN_L: J1.5, R5.2, U5.6 (CANL)
/Power_CAN/CC1: J8.A5 (CC1), R1.1
/Power_CAN/CC2: J8.B5 (CC2), R2.1
/Power_CAN/FUSE_OUT: C8.1, C9.1, U3.5 (OUT), U4.3 (VI)
/Power_CAN/USBDM: R35.1, U7.6 (I/O1)
/Power_CAN/USBDP: R36.1, U7.4 (I/O2)
/Power_CAN/VBUS: C50.1, J8.A4 (VBUS), J8.A9 (VBUS), J8.B4 (VBUS), J8.B9 (VBUS), JP1.1 (A), R21.1, U7.5 (VBUS), U8.4 (VCC)
/RF-915-868/ANT_868: J3.1, RF4.9 (ANT)
/RF-915-868/ANT_915: J2.1, RF3.9 (ANT)
/RF-GNSS_2.4Lora/BACKUP: BT1.P1, C42.1, R16.2, RF1.6 (V_BCKP)
/RF-GNSS_2.4Lora/TP: R17.1, RF1.4 (TIMEPULSE), TP1.1
/SD.MISO: J9.07 (DAT0), U6.36 (PB14)
/SD.MOSI: J9.03 (CMD), U6.37 (PB15)
/SD.NSS: J9.02 (CD/DAT3), R14.2, U6.10 (PC2)
/SD.SCLK: J9.05 (CLK), U6.6 (PF1)
/SW_CLK: J7.2 (SWCLK), U6.50 (PA14)
/SW_DIO: J7.4 (SWDIO), U6.49 (PA13)
/USART1_RX: U6.60 (PB7), U8.7 (TXD)
/USART1_TX: U6.59 (PB6), U8.10 (RXD)
/VDDA: C28.1, C29.1, FB2.1, JP2.1 (A), U6.29 (VDDA)
/XCLK: U6.5 (PF0), X1.3 (OUT)
/~GNSS.RST: C43.1, R26.2, RF1.9 (~RESET), SW4.2 (B), U6.25 (PB1)
GND: BT1.N, C1.2, C2.2, C3.2, C4.2, C5.2, C6.2, C7.2, C8.2, C9.2, C10.2, C11.1, C12.1, C13.2, C14.2, C15.1, C16.1, C17.2, C18.1, C19.1, C20.1, C21.1, C22.2, C23.2, C24.2, C25.2, C26.2, C27.2, C28.2, C29.2, C30.2, C31.2, C32.2, C33.1, C34.1, C35.1, C36.2, C37.2, C38.2, C39.1, C40.2, C41.1, C42.2, C43.2, C44.2, C45.2, C46.2, C47.2, C48.2, C49.2, C50.2, C51.1, C52.1, C53.2, D1.1 (K), D2.1 (K), D3.1 (K), D4.1 (K), D5.1 (K), D6.1 (K), D8.1 (K), D9.1 (K), D10.1 (K), D11.1 (K), D12.1 (K), D13.1 (K), D14.1 (K), D15.1 (K), D16.1 (K), D17.1 (K), D18.1 (K), D19.1 (K), J1.9 (A2), J2.G1, J2.G2, J2.G3, J2.G4, J3.G1, J3.G2, J3.G3, J3.G4, J5.G1, J5.G2, J5.G3, J5.G4, J6.G1, J6.G2, J6.G3, J6.G4, J7.5 (GND), J7.6 (GND), J8.A1 (GND), J8.A12 (GND), J8.B1 (GND), J8.B12 (GND), J9.06 (VSS), R1.2, R2.2, R8.2, R9.2, R19.2, RF1.1 (GND), RF1.10 (GND), RF1.12 (GND), RF2.2 (GND), RF2.15 (GND), RF3.1 (GND), RF3.8 (GND), RF3.10 (GND), RF4.1 (GND), RF4.8 (GND), RF4.10 (GND), SW1.1 (A), SW2.1 (A), SW3.1 (A), SW4.1 (A), SW5.1 (A), SW6.1 (A), SW8.1 (A), U1.1 (GND), U2.1 (GND), U3.1 (GND), U3.9 (PAD), U4.1 (GND), U5.2 (VSS), U6.15 (VSS), U6.27 (VSSA), U6.31 (VSS), U6.47 (VSS), U6.63 (VSS), U7.2 (GND), U8.5 (GND), U8.13 (GND), X1.2 (GND)
unnamed: D1.2 (A), R3.2
unnamed: D2.2 (A), R4.2
unnamed: D3.2 (A), R10.2
unnamed: D4.2 (A), R12.2
unnamed: D5.2 (A), R14.1
unnamed: D6.2 (A), R15.2
unnamed: D7.1 (K), R16.1
unnamed: D8.2 (A), R17.2
unnamed: D9.2 (A), R18.2
unnamed: D10.2 (A), R21.2
unnamed: D11.2 (A), R20.1
unnamed: D12.2 (A), R22.1
unnamed: D13.2 (A), R23.1
unnamed: D14.2 (A), R24.1
unnamed: D15.2 (A), R25.1
unnamed: D16.2 (A), R30.1
unnamed: D17.2 (A), R31.2
unnamed: D18.2 (A), R32.1
unnamed: D19.2 (A), R33.1
unnamed: D20.2 (A), R34.2
unnamed: D20.1 (K), U8.6 (CBUS0)
unnamed: J4.1, RF1.3 (RXD)
unnamed: J4.2, RF1.2 (TXD)
unnamed: J8.A6 (D+), J8.B6 (D+), U7.3 (I/O2)
unnamed: J8.A7 (D-), J8.B7 (D-), U7.1 (I/O1)
unnamed: J9.08 (DAT1), TP6.1
unnamed: J9.01 (DAT2), TP5.1
unnamed: JP2.2 (B), U6.28 (VREF+)
unnamed: RF1.13 (LNA_EN), TP4.1
unnamed: J5.1, RF1.11 (RF_IN)
unnamed: RF1.14 (VCC_RF), TP3.1
unnamed: RF1.18 (~SAFEBOOT), TP2.1
unnamed: J6.1, RF2.1 (ANT)
unnamed: R6.1, R7.1, U3.3 (EN/UVLO)
unnamed: R7.2, R8.1, U3.8 (OVLO)
unnamed: C7.1, U3.2 (dV/dT)
unnamed: R19.1, U5.8 (STBY)
unnamed: C51.2, R35.2, U8.1 (USBDM)
unnamed: C52.2, R36.2, U8.12 (USBDP)

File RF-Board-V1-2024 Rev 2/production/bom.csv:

Designator,Footprint,Quantity,Value,LCSC Part #
BT1,BAT_3034TR,1,3034TR,
"C1, C12, C15, C16, C18, C22, C39, C46, C9",0805,9,10u,
"C10, C2, C47",0805,3,22u,
"C11, C13, C19, C20, C21, C23, C24, C25, C26, C27, C28, C33, C34, C35, C36, C37, C38, C41, C43, C44, C45, C49, C50, C53, C6",0805,25,100n,
"C14, C17, C3, C31, C32, C4, C40, C48, C8",CP_Elec_6.3x5.9,9,100u,
"C29, C30, C42, C5",0805,4,1u,
"C51, C52",0603,2,47p,
C7,0805,1,2n2,
"D1, D10, D11, D12, D13, D14, D15, D16, D17, D18, D19, D20, D3, D4, D5, D6, D8, D9",0603,18,LED,
D2,0603,1,BLUE,
D7,D_SOD-123,1,0.5A/40V/420mV,
FB2,0603,1,120R,
"H1, H2, H3, H4",MountingHole_3.2mm_M3_Pad,4,~,
J1,DB7W2-Male,1,~,
"J2, J3, J6",GRADCONN_RFPC-SMA29-F,3,RFPC-SMA29-F,
J4,PinHeader_1x02_P2.54mm_Vertical,1,UART,
J5,GRADCONN_RFPC-SMA28-F,1,RFPC-SMA28-F,
J7,IDC-STM32-Prog-Header_2x05_P2.54mm_Vertical,1,STM32-Prog-Header,
J8,USB_C_Receptacle_GCT_USB4105-xx-A_16P_TopMnt_Horizontal,1,USB_C_Receptacle_USB2.0_14P,
J9,CUI_MSD-10-C,1,MSD-10-C,
"JP1, JP2",J_0603_Triangular,2,Jumper_2_Open,
JP4,Jumper_Micro-Miniature_P5.375mm,1,Jumper_2_Open,
"R1, R2",0603,2,5k1,
"R10, R12, R14, R15, R17, R18, R31, R34",0603,8,600,
"R11, R13",0603,2,2k2,
R16,0603,1,3k3,
"R19, R26",0603,2,10k,
"R20, R22, R23, R24, R25, R30, R32, R33, R37",0603,9,1k,
"R21, R3",0603,2,2k,
"R27, R28, R29",0603,3,0R,
"R35, R36",0603,2,27R,
R4,0603,1,150,
R5,0603,1,120,
R6,0603,1,287K,
R7,0603,1,57K,
R8,0603,1,47k,
R9,0603,1,1k1,
RF1,ublox_MAX,1,MAX-M10S,
RF2,Vollgo VG2392S240X0M2,1,VG2392S240X0M2,
RF3,HOPERF_RFM9XW_SMD,1,DL-RFM69HC-915M,
RF4,HOPERF_RFM9XW_SMD,1,RFM95W-868S2,
"SW1, SW2, SW3, SW4, SW5, SW6, SW8",SW_PUSH_6mm,7,SW_SPST,
SW7,SW_SPDT_PCM12,1,SW_DPDT_x2,
"TP1, TP2, TP3, TP4, TP5, TP6",TestPoint_Pad_2.0x2.0mm,6,TestPoint,
"U1, U2",TO-252-2,2,AZ1084-3.3,
U3,TI_SO-PowerPAD-8,1,TPS2596,
U4,TO-252-2,1,AZ1084-5.0,
U5,SOIC-8_3.9x4.9mm_P1.27mm,1,MCP2542FD,
U6,LQFP-64_10x10mm_P0.5mm,1,STM32G484RET6,
U7,SOT-23-6,1,USBLC6-2SC6,
U8,DFN-12-1EP_3x3mm,1,FT234XD-R,FT234XD-R
X1,Crystal_SMD_3225-4Pin_3.2x2.5mm,1,OXETDLJANF-8MHZ,
